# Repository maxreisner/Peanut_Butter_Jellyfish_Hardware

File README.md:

# Technical Documentation for Peanut Butter Jellyfish's Phorae System

## Max, Katie, Sav, Zach :)

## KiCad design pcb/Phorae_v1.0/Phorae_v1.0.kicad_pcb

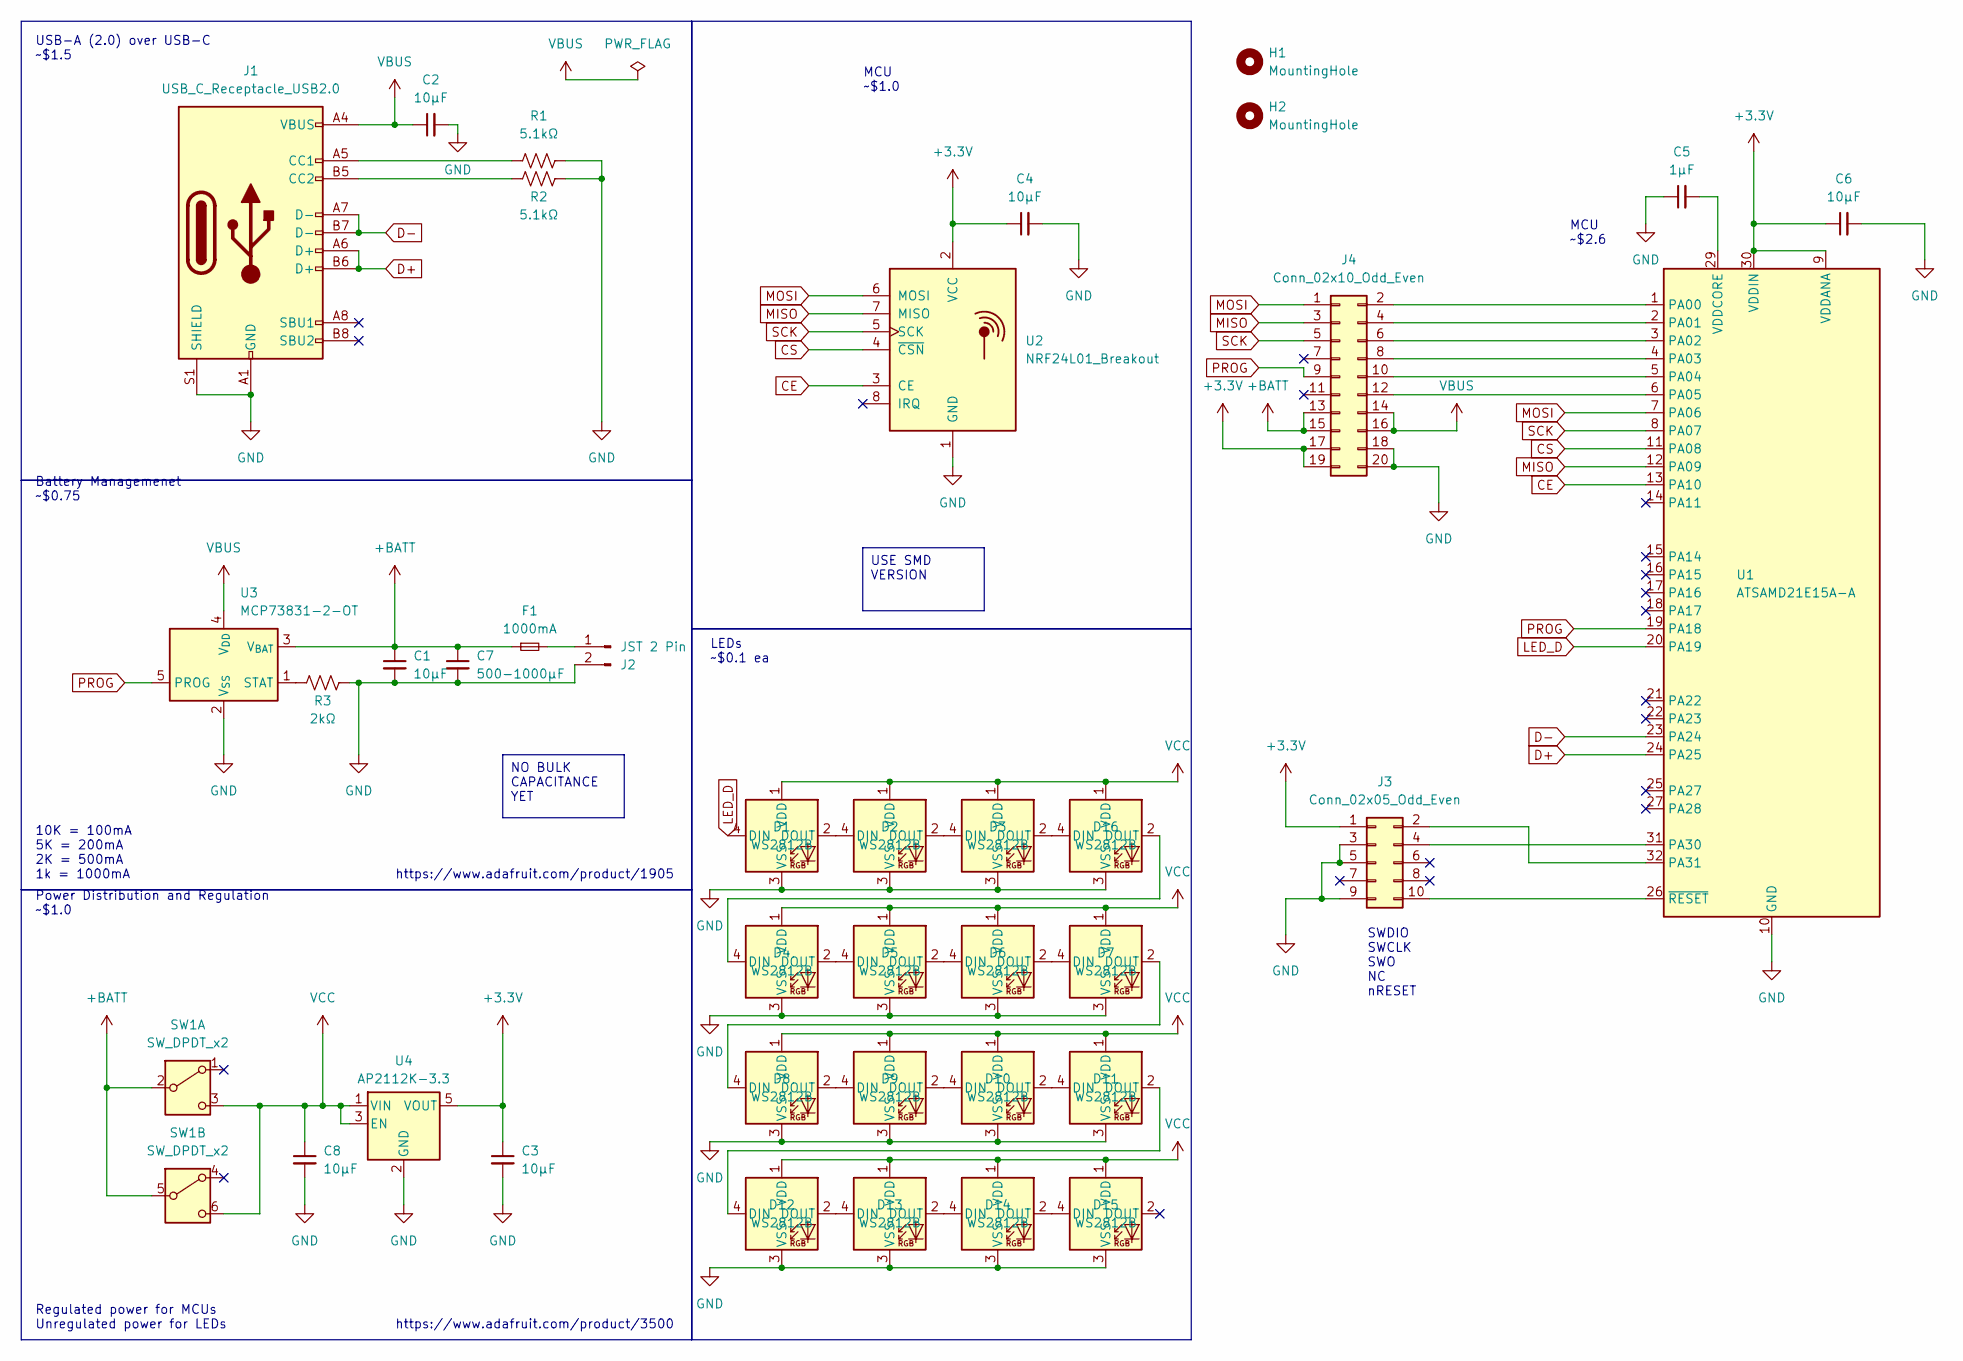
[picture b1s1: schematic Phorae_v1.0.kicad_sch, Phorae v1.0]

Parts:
C1, C2, C3, C4, C6, C8: 10µF; C_0603_1608Metric_Pad1.08x0.95mm_HandSolder
C5: 1µF; C_0603_1608Metric_Pad1.08x0.95mm_HandSolder
C7: 500-1000µF
D1, D2, D3, D4, D5, D6, D7, D8, D9, D10, D11, D12, D13, D14, D15, D16: WS2812B; WS2812-2020_SMD_MICRO
F1: 1000mA; C_0603_1608Metric_Pad1.08x0.95mm_HandSolder
H1, H2: MountingHole; MountingHole_2.2mm_M2
J1: USB_C_Receptacle_USB2.0; USB_C_Receptacle_GCT_USB4110
J2: JST 2 Pin; JST_PH_S2B-PH-SM4-TB_1x02-1MP_P2.00mm_Horizontal
J3: Conn_02x05_Odd_Even; PinHeader_2x05_P2.54mm_Vertical
J4: Conn_02x10_Odd_Even; PinHeader_2x10_P2.54mm_Vertical
R1, R2: 5.1kΩ; C_0603_1608Metric_Pad1.08x0.95mm_HandSolder
R3: 2kΩ; C_0603_1608Metric_Pad1.08x0.95mm_HandSolder
SW1: SW_DPDT_x2; SW_DPDT_CK_JS202011JCQN
U1: ATSAMD21E15A-A; TQFP-32_7x7mm_P0.8mm
U2: NRF24L01_Breakout; NRF24L01_SMD
U3: MCP73831-2-OT; SOT-23-5
U4: AP2112K-3.3; SOT-23-5

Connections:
+3.3V: C3.1, C4.1, C6.1, J3.1, J4.17, J4.19, U1.9 (VDDANA), U1.30 (VDDIN), U2.2 (VCC), U4.5 (VOUT)
+BATT: C1.1, C7.1, F1.1, J4.13, J4.15, SW1.2 (B), SW1.5 (B), U3.3 (V_{BAT})
CE: U1.13 (PA10), U2.3 (CE)
CS: U1.11 (PA08), U2.4 (~CSN)
D+: J1.A6 (D+), J1.B6 (D+), U1.24 (PA25)
D-: J1.A7 (D-), J1.B7 (D-), U1.23 (PA24)
GND: C1.2, C2.2, C3.2, C4.2, C5.1, C6.2, C7.2, C8.2, D1.3 (VSS), D2.3 (VSS), D3.3 (VSS), D4.3 (VSS), D5.3 (VSS), D6.3 (VSS), D7.3 (VSS), D8.3 (VSS), D9.3 (VSS), D10.3 (VSS), D11.3 (VSS), D12.3 (VSS), D13.3 (VSS), D14.3 (VSS), D15.3 (VSS), D16.3 (VSS), J1.A1 (GND), J1.A12 (GND), J1.B1 (GND), J1.B12 (GND), J1.S1 (SHIELD), J2.2, J3.3, J3.5, J3.9, J4.18, J4.20, R1.2, R2.2, R3.1, U1.10 (GND), U1.28 (GND), U2.1 (GND), U3.2 (V_{SS}), U4.2 (GND)
LED_D: D1.4 (DIN), U1.20 (PA19)
MISO: J4.3, U1.12 (PA09), U2.7 (MISO)
MOSI: J4.1, U1.7 (PA06), U2.6 (MOSI)
unnamed: D1.2 (DOUT), D2.4 (DIN)
unnamed: D2.2 (DOUT), D3.4 (DIN)
unnamed: D4.2 (DOUT), D5.4 (DIN)
unnamed: D5.2 (DOUT), D6.4 (DIN)
unnamed: D6.2 (DOUT), D7.4 (DIN)
unnamed: D7.2 (DOUT), D8.4 (DIN)
unnamed: D8.2 (DOUT), D9.4 (DIN)
unnamed: D9.2 (DOUT), D10.4 (DIN)
unnamed: D10.2 (DOUT), D11.4 (DIN)
unnamed: D11.2 (DOUT), D12.4 (DIN)
unnamed: D12.2 (DOUT), D13.4 (DIN)
unnamed: D13.2 (DOUT), D14.4 (DIN)
unnamed: D14.2 (DOUT), D15.4 (DIN)
unnamed: D3.2 (DOUT), D16.4 (DIN)
unnamed: D4.4 (DIN), D16.2 (DOUT)
unnamed: J1.A5 (CC1), R1.1
unnamed: J1.B5 (CC2), R2.1
unnamed: F1.2, J2.1
unnamed: J3.2, U1.32 (PA31)
unnamed: J3.4, U1.31 (PA30)
unnamed: J3.10, U1.26 (~RESET)
unnamed: J4.2, U1.1 (PA00)
unnamed: J4.4, U1.2 (PA01)
unnamed: J4.6, U1.3 (PA02)
unnamed: J4.8, U1.4 (PA03)
unnamed: J4.10, U1.5 (PA04)
unnamed: J4.12, U1.6 (PA05)
unnamed: C5.2, U1.29 (VDDCORE)
unnamed: R3.2, U3.1 (STAT)
PROG: J4.9, U1.19 (PA18), U3.5 (PROG)
SCK: J4.5, U1.8 (PA07), U2.5 (SCK)
VBUS: C2.1, J1.A4 (VBUS), J1.A9 (VBUS), J1.B4 (VBUS), J1.B9 (VBUS), J4.14, J4.16, U3.4 (V_{DD})
VCC: C8.1, D1.1 (VDD), D2.1 (VDD), D3.1 (VDD), D4.1 (VDD), D5.1 (VDD), D6.1 (VDD), D7.1 (VDD), D8.1 (VDD), D9.1 (VDD), D10.1 (VDD), D11.1 (VDD), D12.1 (VDD), D13.1 (VDD), D14.1 (VDD), D15.1 (VDD), D16.1 (VDD), SW1.3 (C), SW1.6 (C), U4.1 (VIN), U4.3 (EN)

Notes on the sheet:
NO BULK CAPACITANCE YET
USE SMD VERSION
Battery Managemenet ~$0.75
MCU ~$1.0
Power Distribution and Regulation ~$1.0
LEDs ~$0.1 ea
10K = 100mA 5K = 200mA 2K = 500mA 1k = 1000mA
https://www.adafruit.com/product/1905
https://www.adafruit.com/product/3500
USB-A (2.0) over USB-C ~$1.5
SWDIO SWCLK SWO NC nRESET
Regulated power for MCUs Unregulated power for LEDs
MCU ~$2.6

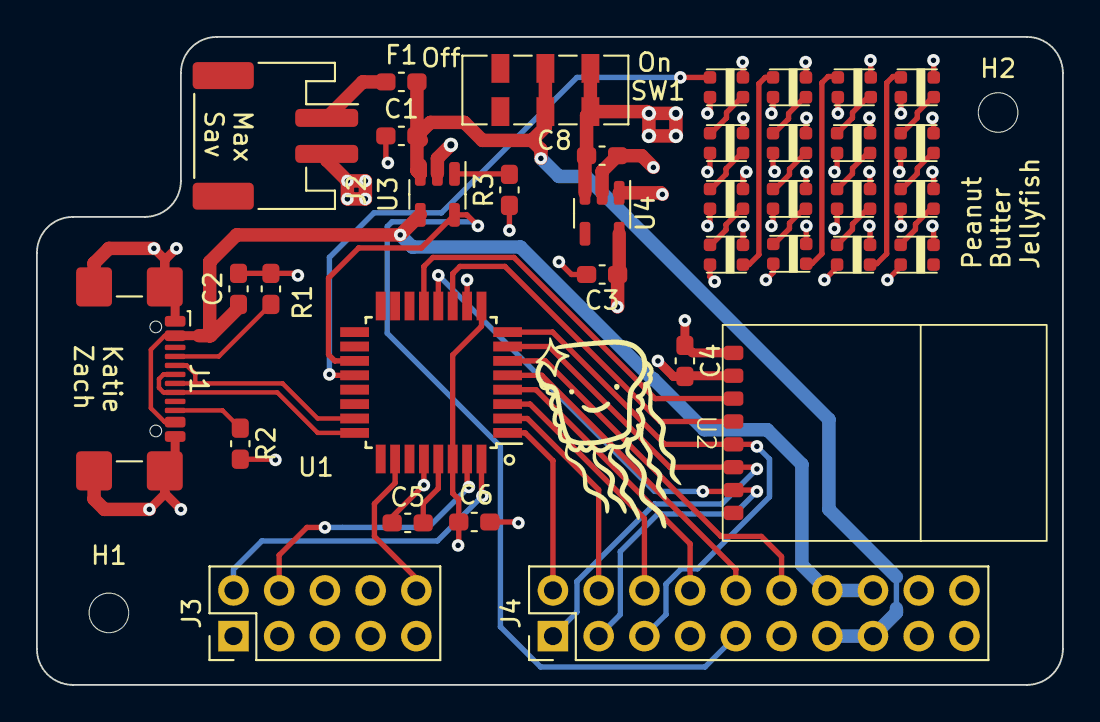
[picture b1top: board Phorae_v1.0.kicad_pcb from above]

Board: 4 copper layers, 57.0 x 36.0 mm, 38 parts (0 on the bottom side), 43 nets.

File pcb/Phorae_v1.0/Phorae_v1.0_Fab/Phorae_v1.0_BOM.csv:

"Id";"Designator";"Footprint";"Quantity";"Designation";"Supplier and ref";
1;"U4";"SOT-23-5";1;"AP2112K-3.3";;;
2;"F1";"C_0603_1608Metric_Pad1.08x0.95mm_HandSolder";1;"1000mA";;;
3;"D15,D2,D13,D6,D8,D11,D16,D4,D3,D1,D10,D12,D9,D7,D14,D5";"WS2812-2020_SMD_MICRO";16;"WS2812B";;;
4;"R1,R2";"C_0603_1608Metric_Pad1.08x0.95mm_HandSolder";2;"5.1kΩ ";;;
5;"J4";"PinHeader_2x10_P2.54mm_Vertical";1;"Conn_02x10_Odd_Even";;;
6;"C2,C1,C4,C8,C3,C6";"C_0603_1608Metric_Pad1.08x0.95mm_HandSolder";6;"10µF";;;
7;"SW1";"SW_DPDT_CK_JS202011JCQN";1;"SW_DPDT_x2";;;
8;"U1";"TQFP-32_7x7mm_P0.8mm";1;"ATSAMD21E15A-A";;;
9;"U3";"SOT-23-5";1;"MCP73831-2-OT";;;
10;"U2";"NRF24L01_SMD";1;"NRF24L01_Breakout";;;
11;"R3";"C_0603_1608Metric_Pad1.08x0.95mm_HandSolder";1;"2kΩ ";;;
12;"J1";"USB_C_Receptacle_GCT_USB4110";1;"USB_C_Receptacle_USB2.0";;;
13;"C5";"C_0603_1608Metric_Pad1.08x0.95mm_HandSolder";1;"1µF";;;
14;"H2,H1";"MountingHole_2.2mm_M2";2;"MountingHole";;;
15;"J3";"PinHeader_2x05_P2.54mm_Vertical";1;"Conn_02x05_Odd_Even";;;
16;"J2";"JST_PH_S2B-PH-SM4-TB_1x02-1MP_P2.00mm_Horizontal";1;"JST 2 Pin ";;;

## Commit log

2024-01-29 Init
2024-01-29 firmware
2024-01-30 lots of layout
2024-02-03 Needs review but v1
2024-02-03 little silkscreen action
2024-02-06 bom analysis
2024-02-19 marked up
2024-03-06 initial firmwar
